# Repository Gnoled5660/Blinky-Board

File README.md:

# Blinky-Board

This is my first ever designed PCB! With no experience and knowledge, I decided to follow a guide that CAN and Tanishq made. Their guide is super well done and gave me everything I needed to understand what I was doing. This PCB is a Blinky Board with a timer, so that the LEDs keep blinking after another. I have never made a PCB before and I was always afraid to make my own, because it seemed so overwhelming. But now I have realised that it isn't that difficult after all. I got familiar with using KiCad and I look forward to design more custom PCBs of my own. 

The first step was to wire the logical symbols. The PCB is mainly split into two section. One section is the clock/timer that sends signals to the LED controller. The other section is the LED controller, that controls the LEDs directly. 

The next step was to assign the footprints. After assigning them, I needed to actually wire them. Since this is a two layer PCB, it was either first layer or second layer. I tried to organize the wires but it felt impossible. In the end, I managed to wire everything. However, it looks super chaotic to me. I will try and do better next time! Some 3D models were not available in KiCad which is why, I had to download them from a website.

I added a bunch of memes on the board, so that it doesn't look empty. It looks really cool to me with all the prints on the board.

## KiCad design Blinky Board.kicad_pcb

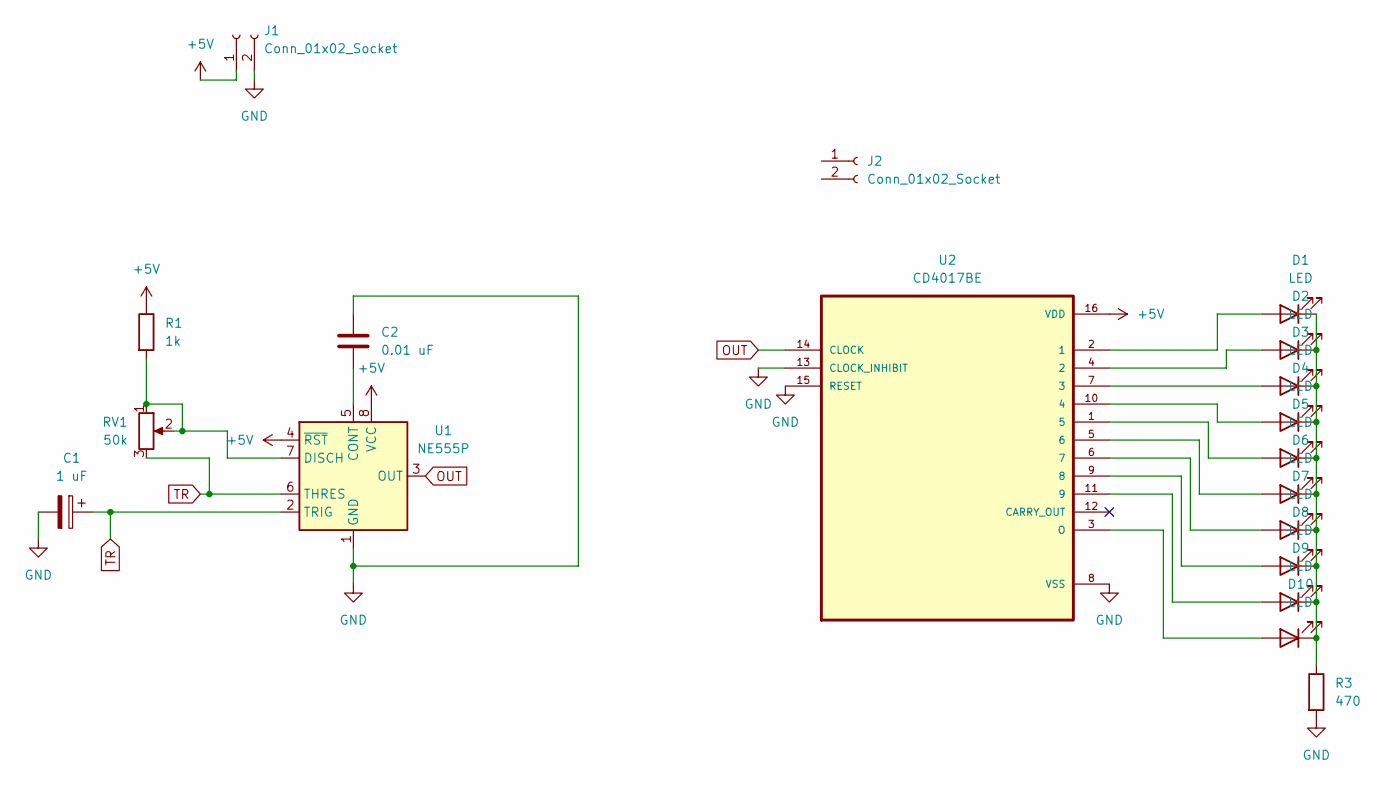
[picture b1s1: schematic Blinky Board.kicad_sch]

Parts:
C1: 1 uF; CP_Radial_D5.0mm_P2.00mm
C2: 0.01 uF; C_Disc_D7.5mm_W2.5mm_P5.00mm
D1, D2, D3, D4, D5, D6, D7, D8, D9, D10: LED; LED_D3.0mm
J1, J2: Conn_01x02_Socket; PinHeader_1x02_P2.54mm_Vertical
R1: 1k; R_Axial_DIN0207_L6.3mm_D2.5mm_P7.62mm_Horizontal
R3: 470; R_Axial_DIN0207_L6.3mm_D2.5mm_P7.62mm_Horizontal
RV1: 50k; Potentiometer_Vishay_T93YA_Vertical
U1: NE555P; DIP-8_W7.62mm
U2: CD4017BE; DIP794W45P254L1969H508Q16

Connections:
+5V: J1.1, R1.1, U1.4 (~RST), U1.8 (VCC), U2.16 (VDD)
GND: C1.2, C2.1, J1.2, R3.2, U1.1 (GND), U2.8 (VSS), U2.13 (CLOCK_INHIBIT), U2.15 (RESET)
unnamed: D1.2 (A), U2.2 (1)
unnamed: D1.1 (K), D2.1 (K), D3.1 (K), D4.1 (K), D5.1 (K), D6.1 (K), D7.1 (K), D8.1 (K), D9.1 (K), D10.1 (K), R3.1
unnamed: D2.2 (A), U2.4 (2)
unnamed: D3.2 (A), U2.7 (3)
unnamed: D4.2 (A), U2.10 (4)
unnamed: D5.2 (A), U2.1 (5)
unnamed: D6.2 (A), U2.5 (6)
unnamed: D7.2 (A), U2.6 (7)
unnamed: D8.2 (A), U2.9 (8)
unnamed: D9.2 (A), U2.11 (9)
unnamed: D10.2 (A), U2.3 (O)
unnamed: C2.2, U1.5 (CONT)
unnamed: R1.2, RV1.1, RV1.2, U1.7 (DISCH)
OUT: U1.3 (OUT), U2.14 (CLOCK)
TR: C1.1, RV1.3, U1.2 (TRIG), U1.6 (THRES)

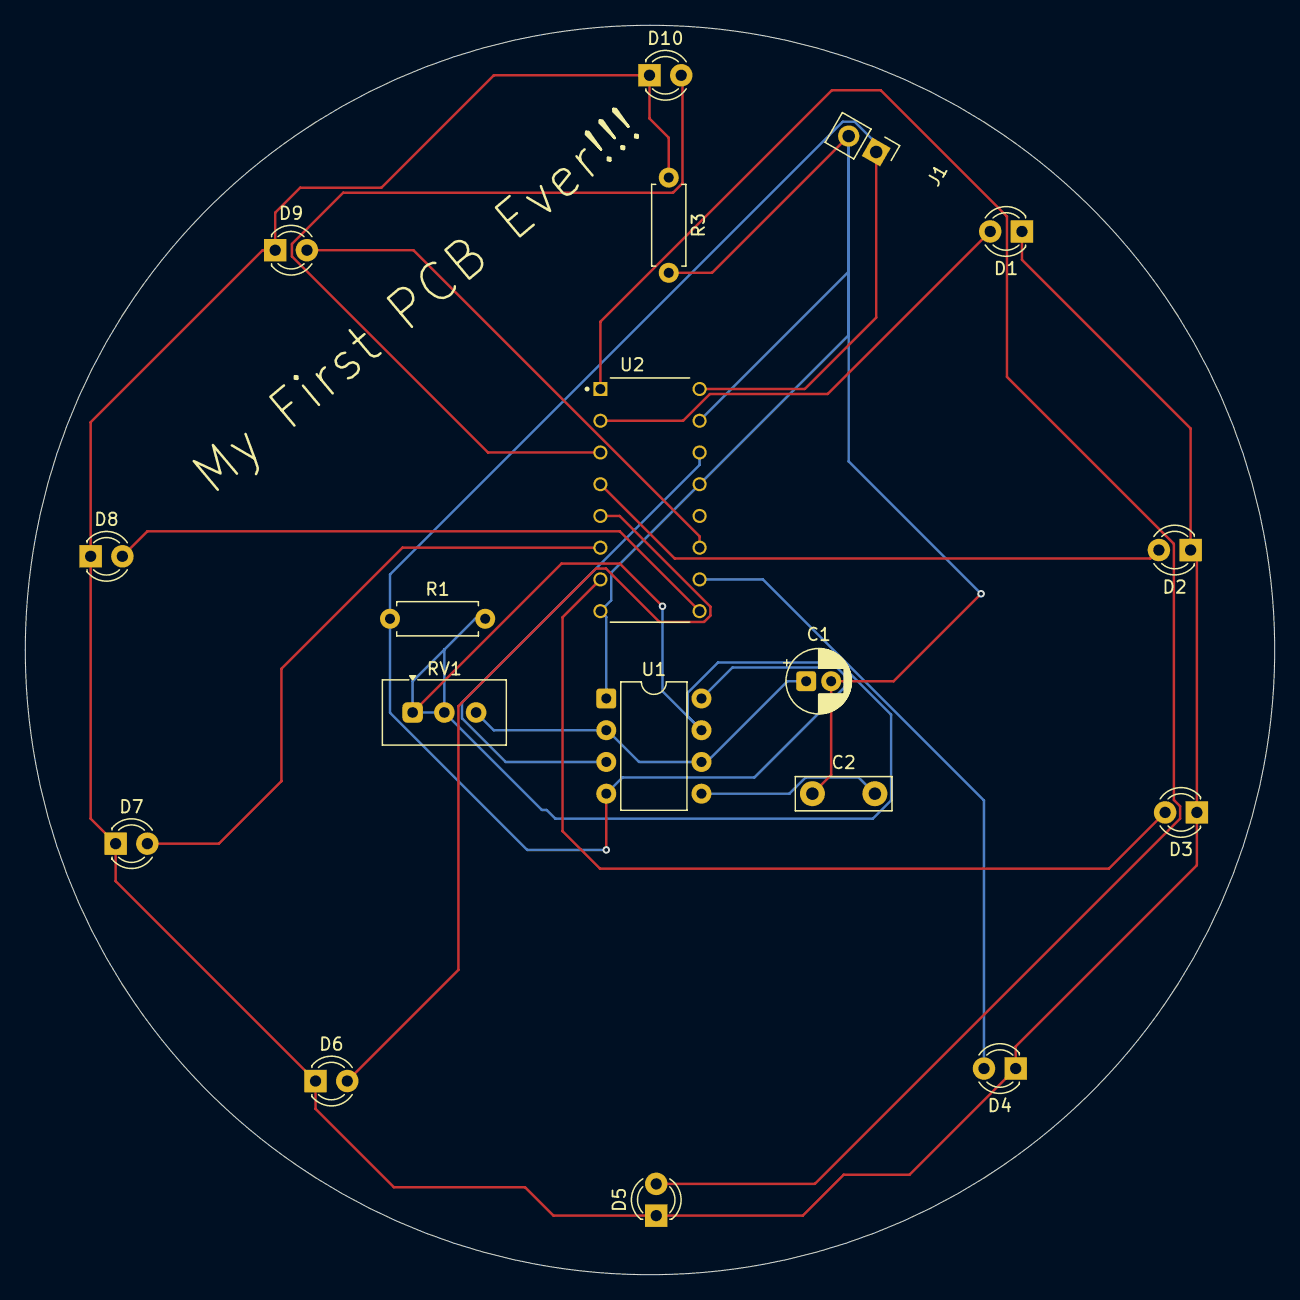
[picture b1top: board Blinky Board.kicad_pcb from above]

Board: 2 copper layers, 100.0 x 100.0 mm, 18 parts (0 on the bottom side), 17 nets.

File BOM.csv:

Product, Cost (USD), Quantity, Purpose, Links
PCB, 9, 1, Main Circuit Board, https://jlcpcb.com
Capacitor, 0.35 ,1, Polarized capacitor, https://funduinoshop.com/en/components/passive-components/ca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
Capacitor, 1.04 ,1, Unpolarized capacitor, https://www.ato.com/0-01μf-100v-ceramic-capacitor?srsltid=Af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
LED, 1.05,10, LED Light, https://www.reichelt.de/de/de/shop/produkt/led_5_mm_bedrahte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
Resistor, 0.15 ,1, Protect LED, https://www.reichelt.de/de/de/shop/produkt/widerstand_metall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
Resistor, 0.08,1, Used as signal transmission, https://www.reichelt.de/de/de/shop/produkt/melf_widerstand_0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
Potentiometer, 2.10,1, regulate LED speed, https://www.reichelt.de/de/de/shop/produkt/praezisionspotent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
NE555P, 0.3, 1, Timer LED light ticks, https://www.reichelt.de/de/de/shop/produkt/timer-ic_typ_555_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
CD4017BE, 1.05,1, Control the LED, https://www.reichelt.de/de/de/shop/produkt/flip-flop_d-type_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

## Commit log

2026-05-29 Create w
2026-05-29 Rename Bildschirmfoto 2026-05-29 um 20.34.48.png to Footprint Wiring.png
2026-05-29 Rename Bildschirmfoto 2026-05-29 um 20.56.26.png to Schematic Symbol.png
2026-05-30 Update links in BOM.csv for PCB and components
2026-05-30 Rename Unbenannte Tabelle - BOM-3.csv to BOM-3.csv
2026-05-30 Rename BOM-3.csv to BOM.csv
